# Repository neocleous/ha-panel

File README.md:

# Home Assistant Touch Panel

A desk-mounted Home Assistant touch panel, vibe coded from start to finish — the software in this repo was written end-to-end by an AI assistant (Claude) in conversation with the maintainer, hardware debugging included. Read it with that in mind; it runs a real panel every day, but nobody hand-crafted it.

Built on a Raspberry Pi 5 with a Waveshare 8" DSI touchscreen, environmental sensors, capacitive touch buttons, and a 3D-printable desk-stand enclosure ([STEP file](https://github.com/neocleous/ha-panel/blob/docs/enclosure/HA%20Panel%20Final.step) on the `docs` branch). Home Assistant runs on a separate server — each panel is a pure display and sensor client, no HAOS on the panel itself.

## What it does

- **Kiosk dashboard** — Chromium in app mode under labwc (Wayland), portrait, no window chrome, with a working on-screen keyboard (squeekboard)
- **Screen sleep** — backlight off after touch inactivity; the wake tap is swallowed via an evdev grab so it never presses anything in the UI
- **Auto-brightness** — backlight follows ambient light from the VEML6030, delivered over MQTT
- **Dark mode** — follows sunset/sunrise via a retained MQTT topic published by an HA automation; Chromium restarts with `--force-dark-mode`
- **Environmental sensors** — temperature, humidity, pressure, VOC (BME680) and ambient light, auto-registered in HA via MQTT discovery
- **Physical buttons** — four capacitive touch buttons (AT42QT1070 on a custom PCB) that work even with the screen asleep
- **Self-updating** — nightly systemd timer runs a full unattended OS + firmware + repo update, showing a progress splash if anyone touches the screen mid-update
- **Zero-touch provisioning** — the [Panel Setup](tools/panel-setup/) app writes first-boot files to a freshly flashed SD card; the panel installs itself and boots into the dashboard in 10–15 minutes (two reboots)

## Hardware

Full parts list with sourcing links: **[BOM.md](BOM.md)**

| Component | Part |
|-----------|------|
| Compute | Raspberry Pi 5 (4 GB) |
| Display | Waveshare 8inch DSI LCD (C), 1280×800 IPS, portrait |
| Touch buttons | AT42QT1070 on a custom PCB (I2C 0x1B, 4 capacitive electrodes) |
| Temp / humidity / pressure / VOC | BME680 breakout (I2C 0x77) |
| Ambient light | VEML6030 breakout (I2C 0x48) |
| Proximity | VL53L0X breakout (I2C 0x29) |
| Power | USB-C (Adafruit USB Type C vertical breakout) |
| Enclosure | 3D-printed desk stand — STEP on the `docs` branch |

All sensors sit on the Pi's I2C bus 1. The sensor cluster lives at the base of the stand, ventilated top-to-bottom, away from display/Pi heat.

## Deploying a panel

The easy way — **[Panel Setup](tools/panel-setup/)** (macOS / Windows / Linux, single binary, no dependencies):

1. Flash Raspberry Pi OS Lite (64-bit) with Raspberry Pi Imager — **no** Imager customisation
2. Run Panel Setup, fill the form (it tests your MQTT credentials against the broker and your Home Assistant URL before letting you write)
3. It writes `userconf.txt`, `firstrun.sh` and the first-boot hook in `cmdline.txt` to the SD card
4. Insert, power on, wait 10–15 minutes. The first boot configures the panel and reboots; the second installs everything (progress on screen) and reboots into your dashboard. Logs: `firstrun.log` and `firstboot.log` on the SD card — details in [tools/panel-setup/README.md](tools/panel-setup/README.md#what-the-first-boot-does)

Binaries on the [Releases page](../../releases); build details and the unsigned-app first-run notes are in [tools/panel-setup/README.md](tools/panel-setup/README.md).

The manual way — SSH install with `system/install.sh` — is documented in [system/README.md](system/README.md).

## Repository layout

```
ha-panel/
├── sensor-daemon/        # MQTT discovery + I2C polling (systemd service)
│   └── sensors/          # AT42QT1070, BME680, VL53L0X, VEML6030 drivers
├── system/               # Kiosk stack: startup.sh, screen-sleep.py,
│                         # nightly update.sh + timer, update splash
├── provisioning-ui/      # On-device touchscreen setup wizard
└── tools/panel-setup/    # Cross-platform SD-card preparation app (Go)
```

Per-panel state lives outside the repo on the device (`/opt/ha-panel/config` and `/opt/ha-panel/sensor-config.py`) and survives the nightly `git reset --hard`. **Never commit credentials to this repo.**

## How the kiosk works

```
TTY1 autologin (.bash_profile)
  └── startup.sh
        ├── sources /opt/ha-panel/config
        ├── writes labwc rc.xml   (touch→output mapping, undecorated maximised windows)
        ├── writes labwc autostart (screen-sleep, squeekboard, chromium loop)
        └── exec labwc
              ├── screen-sleep.py  (sleep/wake + auto-brightness + theme switch)
              ├── squeekboard      (on-screen keyboard)
              └── chromium --app=<HA dashboard>  (restarts on crash/theme/update)
```

MQTT topics follow `home/<panel-id>/…`; the fleet-wide dark-mode topic is `home/panels/theme`.

## SSH access

Panels accept SSH from the local /24 only (nftables). `ssh you@panel-01.local`.

## Troubleshooting

First stops: `/var/log/ha-panel-startup.log` on the panel, `journalctl -u sensor-daemon`, `/var/log/ha-panel-update.log` for the nightly update, and `firstrun.log` / `firstboot.log` on the SD card's boot partition if first boot fails. More in [system/README.md](system/README.md).

## License

[PolyForm Noncommercial 1.0.0](LICENSE.md) — free for personal, hobby, educational, and other noncommercial use: build panels, modify the code, share it. **Commercial use is not permitted.** If you want to use this commercially, contact the maintainer about a separate license.

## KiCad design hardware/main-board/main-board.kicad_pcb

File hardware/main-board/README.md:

# HA panel — main board

> **Rev 3.2 (2026-11-14): the board in this folder.** Rev 3.1 with a relief in the side edge on the left-speaker side
> (floor at u +42.0 over v +1.5 ... +13.0, 1.5 deep, inner corners r 1.0) for the ReSpeaker's USB-C plug and the pliers
> that pull it. No part moved; the amplifier's GPIO2 via and the I2C pair's loop on the back face were laid inside the
> new edge, and the pours follow it (Daniel's decision of 2026-11-14). ERC 0 errors 0 warnings; DRC 0 errors, 0 open
> connections, schematic comparison clean, 2 warnings. Report: [`rev3.2/README.md`](rev3.2/README.md). For the enclosure
> model: [`main-board-rev3-2-reply-2026-11-14.md`](main-board-rev3-2-reply-2026-11-14.md), [`MAIN_env.md`](MAIN_env.md),
> `main-board-rev3.2.step`; the plug envelopes of rev 3.1 stand (`main-board-rev3.1-plug-envelopes.step`). Rev 3.1's
> files are kept (`rev3.1/`, `main-board-rev3.1.step`, `main-board-rev3.1-plug-envelopes.step`,
> `main-board-rev3-1-reply-2026-11-11.md`). No fab files for rev 3, 3.1 or 3.2.
>
> **Rev 3.1 (2026-11-11): its board file is now `rev3.1/main-board-rev3.1.kicad_pcb`.** Rev 3 with three changes asked for by the enclosure (top right
> hole at u +19.20, v +25.00; BME680 header 3.90 further from the radar socket; VEML6030 header 1.00 lower), wider
> copper for the Pi's 5 V and the 20 V inlet, and ground pours on both outer layers. Same circuit, same parts.
> ERC 0 errors 0 warnings; DRC 0 errors, 0 open connections, schematic comparison clean, 2 warnings.
> Report: [`rev3.1/README.md`](rev3.1/README.md). For the enclosure model:
> [`main-board-rev3-1-reply-2026-11-11.md`](main-board-rev3-1-reply-2026-11-11.md), [`rev3.1/MAIN_env.md`](rev3.1/MAIN_env.md),
> `main-board-rev3.1.step`, `main-board-rev3.1-plug-envelopes.step`. Pi lead table: [`gpio-leads.md`](gpio-leads.md).
> The rev 3 files are kept (`rev3/`, `main-board-rev3.step`, `main-board-rev3-plug-envelopes.step`,
> `main-board-rev3-reply-2026-11-11.md`). No fab files for rev 3 or rev 3.1.
>
> **Rev 3 (2026-11-11): schematic and routed board for the site behind the display.**
> 87.0 x 57.9, four layers, every part on the door side. ERC 0 errors 0 warnings; DRC 0 errors, 0 open connections,
> schematic comparison clean, 2 warnings. Report: [`rev3/README.md`](rev3/README.md) (floor plan: sections 1 to 13, routed
> board: section 14). Pi lead table: [`rev3/gpio-leads.md`](rev3/gpio-leads.md). For the enclosure model:
> [`main-board-rev3-reply-2026-11-11.md`](main-board-rev3-reply-2026-11-11.md), [`rev3/MAIN_env.md`](rev3/MAIN_env.md),
> `main-board-rev3.step`, `main-board-rev3-plug-envelopes.step`. The board file of rev 3 is
> `rev3/main-board-rev3.kicad_pcb`.
> **Everything below this note describes rev 2.1**, whose files are now in [`rev2.1/`](rev2.1/). All of it is a draft
> until the whole unit is shown to be buildable (architect log 2026-11-10, section 0).

Status: **block 3 done (2026-11-09) — layout rev 2.1, single-sided SMD, routed, DRC clean; fab files, BOM, assembly notes and drawing issued.** Rev 2.1 moves C7 to the top strip so every front lead plugs after mounting (`MAIN_env.md`).

- **KiCad 9.0.9.** Open `main-board.kicad_pro`. Project libraries: `lib/ha_panel.kicad_sym` (custom symbols: TAS5756M, TPS16630, NID100-5, TPS70933, +20V power symbol) and `lib/ha_panel.pretty` (custom footprints, created in block 2).
- **Schematic PDF:** `main-board-schematic.pdf` (5 pages).
- **ERC:** 0 errors, 0 warnings (`erc-report.txt`). **DRC:** 0 errors, 0 unconnected, parity clean, 2 warnings (J2 silk trimmed at the board edge, J4 courtyard trimmed to its wire pads) (`drc-report.txt`).
- **Board:** 90 × 55, 4 layers (F parts + signals / In1 GND / In2 +5V, +20V, PVDD / B signals). Every SMD part on the front; the back carries only J2, LK1, through-hole joints and bare test pads. Renders: `main-board-routed-3d.png` (front, back), `main-board-copper-F-B.png` (front copper, back copper mirrored). Layout notes: `NOTES.md` §7; envelope: `MAIN_env.md`.
- **Fab (JLC, bare board):** `fab/main-board-jlc-2026-11-08.zip`; order options and what the files use against JLC's limits in `../notes/jlc-fab.md`. **Stencil:** the main-board area of the combined stencil `../stencil/` (D57).
- **Assembly drawing:** `main-board-assembly.pdf` (A3; front and back, DNP crossed out), from `gen/assembly_drawings.py`. Assembly and bring-up: below.
- **Notes with every value's source:** `NOTES.md`. **GPIO lead pin table and plug maps:** `gpio-leads.md`.
- `gen/` holds the Python that generated the schematic and the layout (sheet builder, footprints, placement, TAS escape, maze router, Freerouting driver, silk placement). The KiCad files are the source of truth; the scripts are kept for provenance (symbol UUIDs are deterministic, so a schematic regeneration keeps the PCB links; a layout regeneration routes differently, see NOTES §7).

## Sheets
1. Root — index.
2. **20 V inlet and eFuse** — J1 (5807 pigtail) → F1 0453005.MR → TPS16630 (UVLO 17.05 V, OVP 24.06 V, I_OL 3.28 A, dV/dt 19.6 ms) → +20V bus with SMBJ22A.
3. **5 V supply and outputs** — Mean Well EMC circuit (120 µF – SRR1260-150M – 120 µF) → NID100-5 (enabled by the eFuse PGOOD) → 22 µF + SMBJ6.0A-E → Pi branch (0453010.MR → wire link LK1 → USB4085-GF-A, Rp 10 kΩ) and radar branch (0453001.MR). DNP trim network R8/R9.
4. **3.3 V, Pi link, XH, D4a** — TPS70933 LDO (EN = Pi 3V3) → sensor PTC and amp logic rail; GPIO landing J3/J4 (13 wire pads); radar and touch XH headers; D4a ReSpeaker tap J7 with six DNP 0 Ω links.
5. **Amplifier** — TAS5756M stereo BTL per SLAS988B Fig. 79 / Table 22 with the DigiAMP+ wiring (`rpi-digiampplus`: I²C 0x4C, GPIO22 mute), 20 dBV at 768 kHz, type-2 LC 10 µH + 0.68 µF, speaker XH headers.

## Default fit (spin 1)
| Option | Default | Alternative |
|---|---|---|
| Echo reference (D4a) | **Topology A, USB reference**: R20–R25 open | Topology B, I²S reference: fit R20–R23 (+R24/R25), I²S firmware, Pi as I²S clock consumer |
| NID trim (V20) | R8, R9 open (5.0 V) | R8 Trim→Com raises Vout; value found on the bench via TP13 |
| Amp logic rail | R26 fitted (board LDO) | R27 instead of R26 (Pi 3V3) |
| I²S series | R14–R16 0 Ω | 22–47 Ω if edges ring |
| NID enable | R7 0 Ω (eFuse PGOOD) | R7 open = NID free-running |
| Pi branch | LK1 wire fitted | LK1 open + 10 A meter (bench 2.7) |

## Assembly (block 3, 2026-11-09)
One hotplate pass for every SMD part (front), then the THT parts with the iron. Drawing: `main-board-assembly.pdf`.

**Before you start**
- Paste: Sn63/Pb37 no-clean, as on rev C (Chip Quik SMD291AXT4, `hardware/rev-c/README.md`). Stencil: the main-board area of `../stencil/`, 0.12 mm.
- U100 (TAS5756M) is MSL 3: "Level-3-260C-168 HR" (TI package option addendum in the datasheet), i.e. 168 h at ≤ 30 °C / 60 % RH once its moisture bag is open. Open the bag on build day. If it has been open longer, bake per J-STD-033 before reflow.
- Bare board, meter on ohms: +20V (TP2), PVDD (F5 pin 2), +5V (TP9) and 3V3 (TP16) to GND (TP7) must read open.

**Build order**
1. Paste the front through the stencil. Place every SMD part except the DNPs: R8, R9, R20–R25, R27 (crossed out on the drawing).
   - Polarity: D1 SMBJ22A, D2 SMBJ6.0A-E (band = cathode).
   - Pin 1: U1 TPS16630, U2 TPS70933, U100 TAS5756M (chamfered corner on the drawing).
2. Hotplate with the back down (nothing is on the back yet). Profile below.
3. Inspect U100 (0.5 mm pitch) and U1 (0.65 mm) under magnification for bridges and lifted pins.
4. Iron, door side first, because these joints are on the front among the SMD parts:
   - J2 USB4085 (16 contacts, 4 shell stakes), mouth flush with the bottom edge;
   - LK1, 1.0 mm tinned copper wire.
5. Iron, front parts soldered on the back, low to high: J10 (2 × 4 header), J1, J5, J6, J8, J9 (XH), C7, C5, C6 (+ to the + mark), PS1 NID100-5 last.
6. J3/J4 take the GPIO lead wires (`gpio-leads.md`, `../notes/harness.md`). J7 stays empty in topology A.

**Hotplate profile**
- Follow the paste maker's profile. Chip Quik's chart for SMD291AX (datasheet rev 1.1) runs 25 → 100 → 150 °C (preheat and soak), crosses the 183 °C liquidus and tops at 235 °C, about 240 s in all.
- U100 is rated 260 °C peak (TI, above), so a Sn63/Pb37 profile stays below its limit.
- Thermal pad (pin 49): the stencil's 2 × 4 windows give 72.8 % paste coverage. SLAS988B 11.1.3.2 asks for 70–80 %. The 39 vias under the pad are in the footprint.
- The paste's flux is "Synthetic No-Clean" (Chip Quik), so nothing is washed.

**Default fit:** the table above. All D4a links open (topology A), R26 fitted, LK1 fitted.

## Bring-up (bench, board out of the enclosure)
Meter only; test pads are on the back (`NOTES.md` §5). Ground: TP7, TP15, TP17 or TP20.

**Stage 1: 20 V only.** The 5807 + charger on J1; no Pi, leads or sensors.

| Probe | Expect | Why |
|---|---|---|
| TP1 VIN, TP2 20V, TP8 NID_IN, F5 pin 2 (PVDD; front, bench only) | ≈ 20 V, all equal | eFuse on above UVLO 17.05 V; OVP at 24.06 V (`NOTES.md` §1) |
| TP3 IMON | 0.279 V/A × bus current: record it | eq. 9, `NOTES.md` §1 |
| TP6 SHDN | ≈ 2.7 V | internal open-circuit voltage (SLVSET9G 6.5) |
| TP9 5V; TP10 5V_F, TP11 EXT5V, TP12 RADAR | 4.90–5.10 V, all ≈ equal | NID100-5 ± 2 % (bench plan 2.12) |
| TP13 TRIM | record (V20) | `NOTES.md` §2 |
| TP16 3V3, TP19 FAULT, TP4 FLT | ≈ 0 V | The LDO waits for the Pi's 3V3 on lead A1 (EN, R13 pull-down); FLT and FAULT are pulled up to rails that are still off. |

**Stage 2: Pi on.**
- Connect:
  - J2 → Pi USB-C;
  - GPIO plugs A and B;
  - the LCD lead per `../notes/harness.md`: 5 V and GND at Pi pins 2/6. Insulate and tie back its SDA/SCL wires (V22).
- Expect:

| Probe | Expect | Why |
|---|---|---|
| TP16 3V3 | 3.267–3.333 V | TPS70933 ± 1 % (SBVS186H) |
| TP4 FLT, TP19 FAULT | ≈ 3.3 V | no eFuse fault, no amp fault |
| `vcgencmd get_throttled` | `0x0` | bench plan 2.6 |
| `vcgencmd pmic_read_adc EXT5V_V` | ≥ 4.87 V under load | bench plan 2.6 |

**Stage 3: config and buses.** Apply `../notes/pi-config.md`, then plug the sensors (J10), the touch lead (J6) and the radar (J5).
- `sudo i2cdetect -y 1`: **1b** (touch), **48** (VEML6030), **UU** at 4c (TAS5756M, held by the `rpi-digiampplus` driver), **77** (BME680).
- Radar: record TP12 with the LD2410C running (the rail's worst case is 4.90 V; the LD2410C manual gives 5–12 V). Expect 0 invalid frames at 256000 8N1 on `/dev/ttyAMA0` (bench plan 1.5, 2.12).
- Then bench plan stage 2 (2.1–2.12).

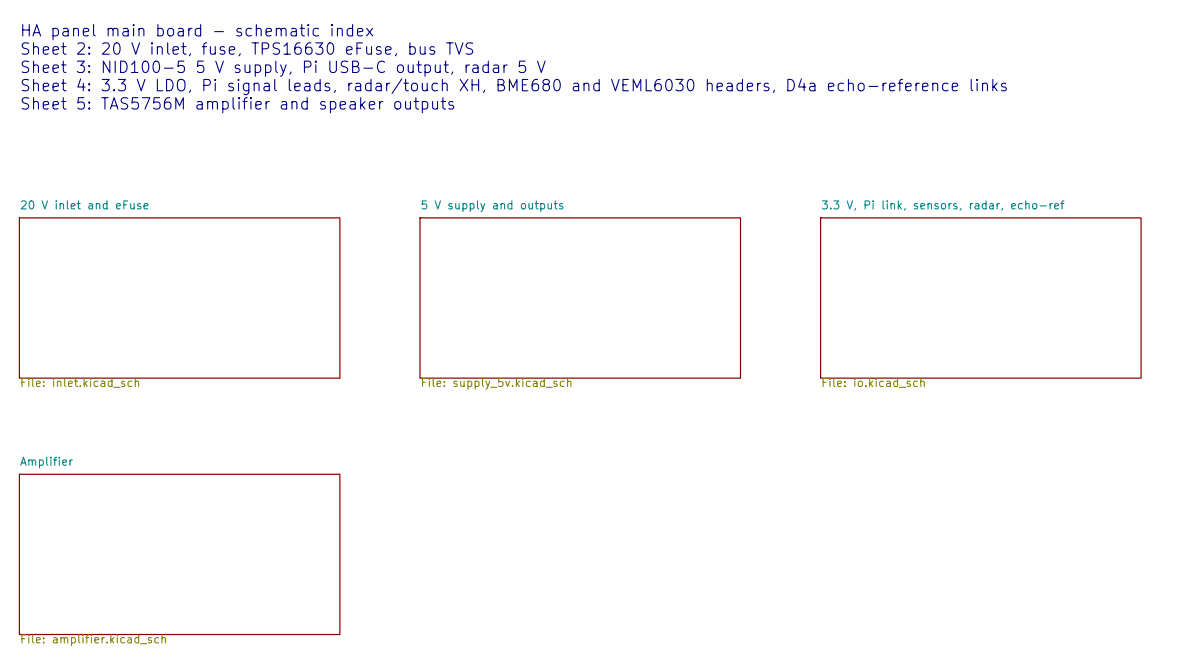
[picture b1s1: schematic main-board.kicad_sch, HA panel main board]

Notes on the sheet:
HA panel main board - schematic index Sheet 2: 20 V inlet, fuse, TPS16630 eFuse, bus TVS Sheet 3: NID100-5 5 V supply, Pi USB-C output, radar 5 V Sheet 4: 3.3 V LDO, Pi signal leads, radar/touch XH, BME680 and VEML6030 headers, D4a echo-reference links Sheet 5: TAS5756M amplifier and speaker outputs

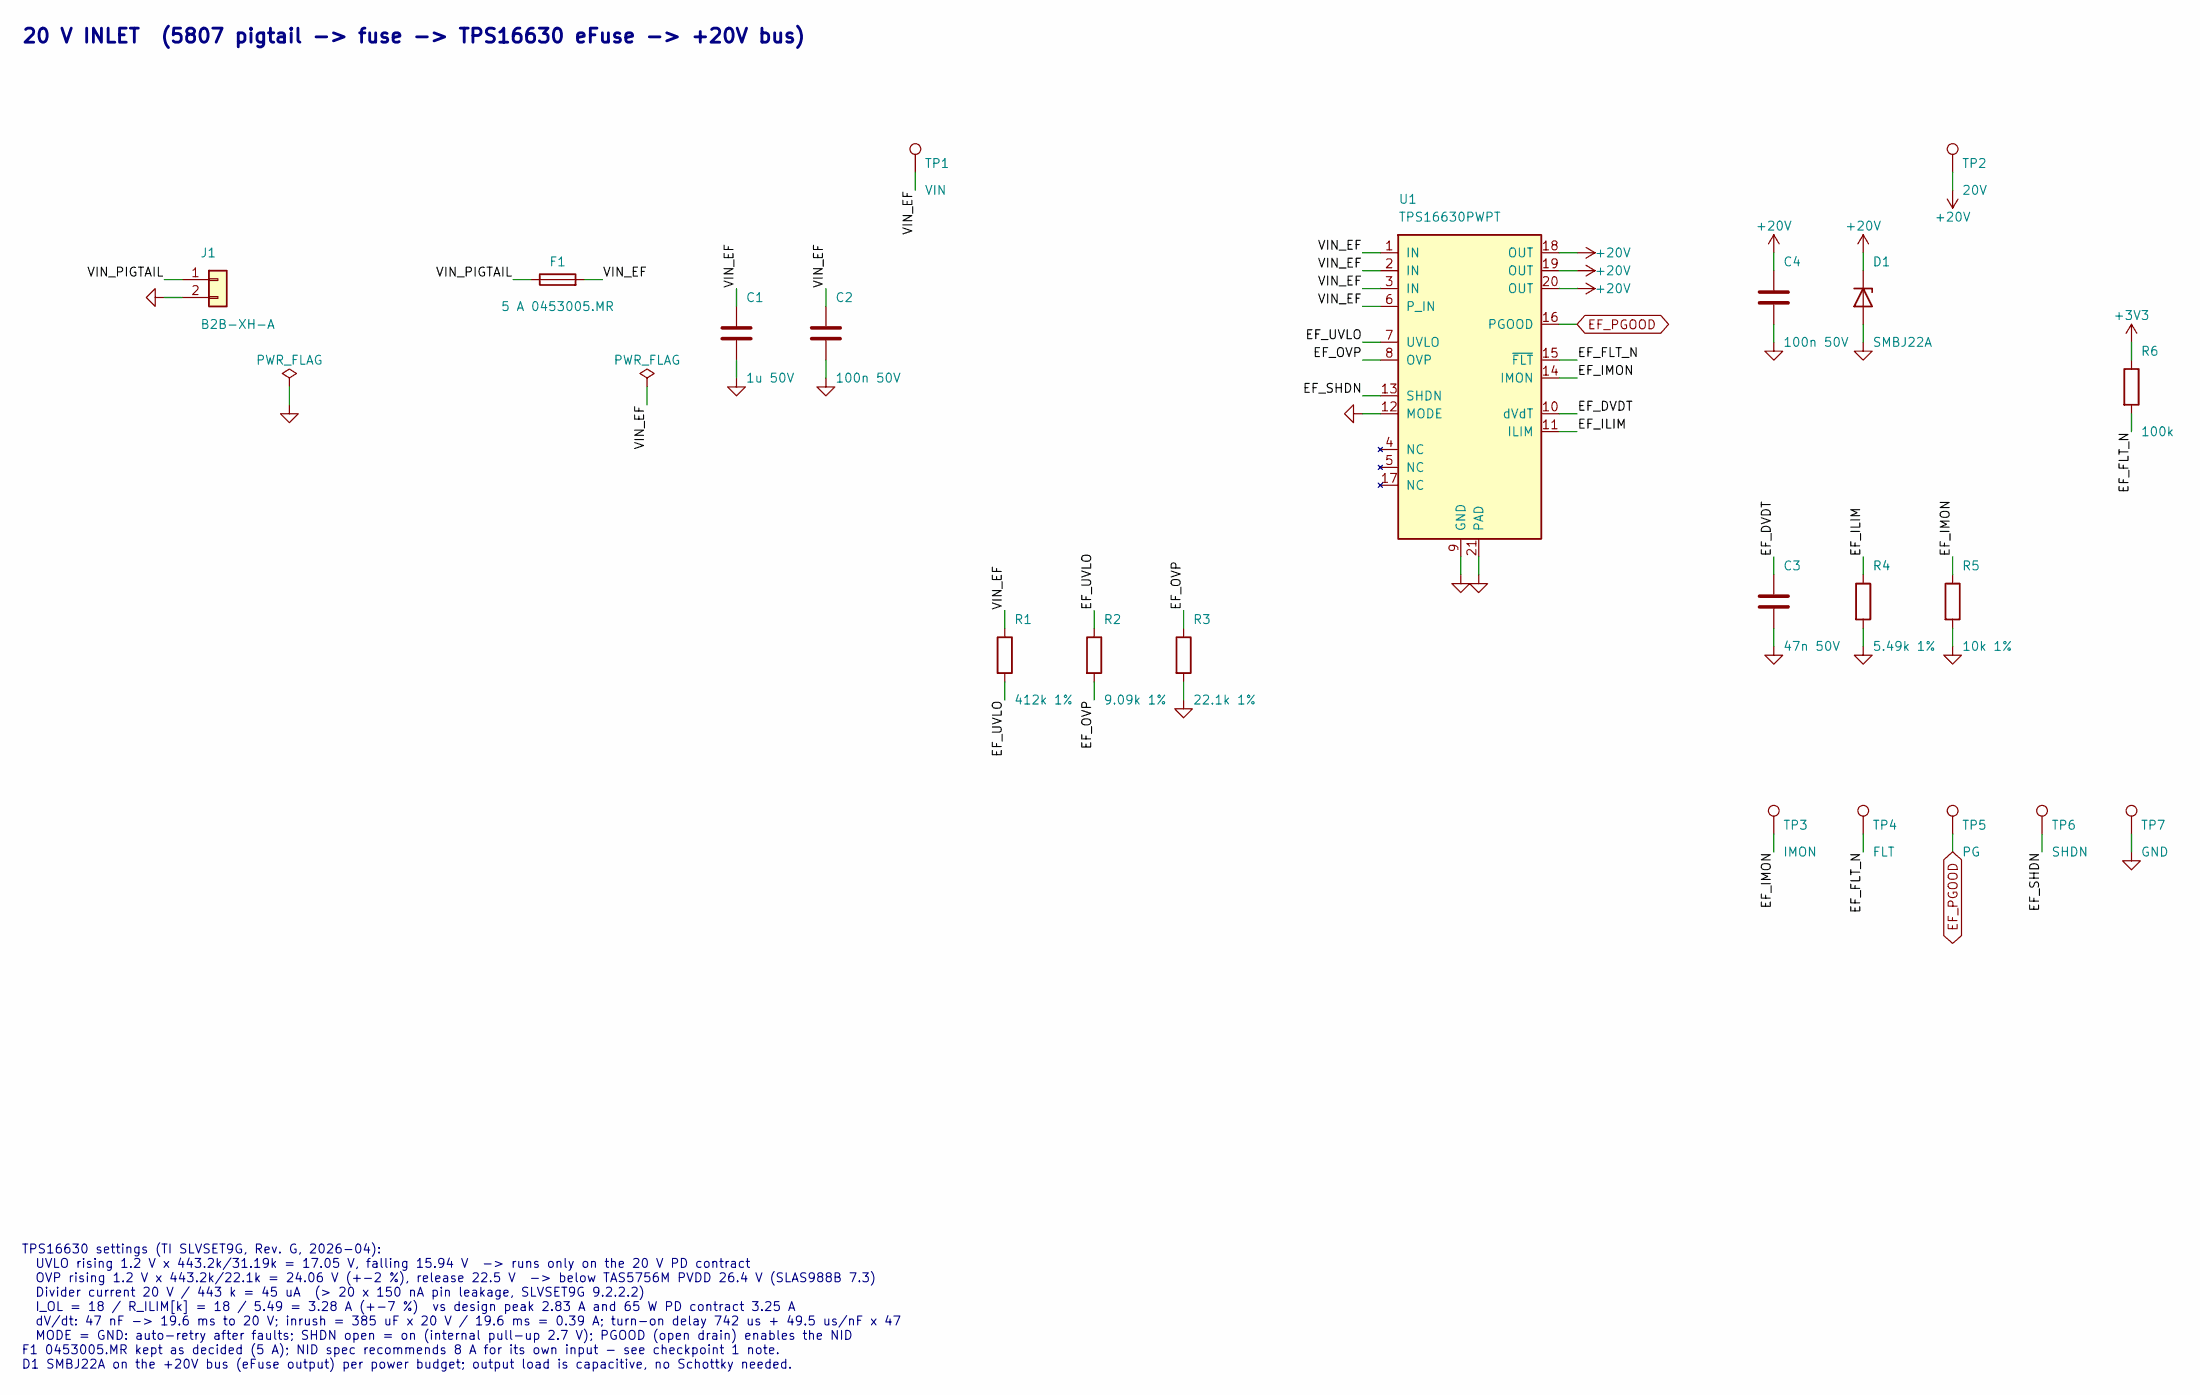
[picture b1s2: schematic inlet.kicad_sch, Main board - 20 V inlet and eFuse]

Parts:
C1: 1u 50V; C_0805_2012Metric; MPN 08055C105KAT2A; DigiKey 478-KGM21AR71H105KUCT-ND
C2, C4: 100n 50V; C_0603_1608Metric; MPN CC0603KRX7R9BB104; DigiKey 311-1344-1-ND
C3: 47n 50V; C_0603_1608Metric; MPN CL10B473KB8NNNC; DigiKey 1276-1063-1-ND
D1: SMBJ22A; D_SMB; MPN SMBJ22A; DigiKey SMBJ22ALFCT-ND
F1: 5 A 0453005.MR; Fuse_Littelfuse-NANO2-451_453; MPN 0453005.MR; DigiKey F3139CT-ND
J1: B2B-XH-A; JST_XH_B2B-XH-A_1x02_P2.50mm_Vertical; MPN B2B-XH-A; DigiKey 455-B2B-XH-A-ND
R1: 412k 1%; R_0603_1608Metric; MPN RC0603FR-07412KL; DigiKey 311-412KHRCT-ND
R2: 9.09k 1%; R_0603_1608Metric; MPN RC0603FR-079K09L; DigiKey 311-9.09KHRCT-ND
R3: 22.1k 1%; R_0603_1608Metric; MPN RC0603FR-0722K1L; DigiKey 311-22.1KHRCT-ND
R4: 5.49k 1%; R_0603_1608Metric; MPN RC0603FR-075K49L; DigiKey 311-5.49KHRCT-ND
R5: 10k 1%; R_0603_1608Metric; MPN RMCF0603FT10K0; DigiKey RMCF0603FT10K0CT-ND
R6: 100k; R_0603_1608Metric; MPN RMCF0603FT100K; DigiKey RMCF0603FT100KCT-ND
TP1: VIN; TestPoint_Pad_D1.5mm
TP2: 20V; TestPoint_Pad_D1.5mm
TP3: IMON; TestPoint_Pad_D1.5mm
TP4: FLT; TestPoint_Pad_D1.5mm
TP5: PG; TestPoint_Pad_D1.5mm
TP6: SHDN; TestPoint_Pad_D1.5mm
TP7: GND; TestPoint_Pad_D1.5mm
U1: TPS16630PWPT; HTSSOP-20-1EP_4.4x6.5mm_P0.65mm_EP3.4x6.5mm_Mask2.96x2.96mm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; MPN TPS16630PWPT; DigiKey 296-TPS16630PWPTCT-ND

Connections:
+3V3: R6.1; also elsewhere on the board
+20V: C4.1, D1.1 (K), TP2.1, U1.18 (OUT), U1.19 (OUT), U1.20 (OUT); also elsewhere on the board
/20 V inlet and eFuse/EF_DVDT: C3.1, U1.10 (dVdT)
/20 V inlet and eFuse/EF_FLT_N: R6.2, TP4.1, U1.15 (~FLT)
/20 V inlet and eFuse/EF_ILIM: R4.1, U1.11 (ILIM)
/20 V inlet and eFuse/EF_IMON: R5.1, TP3.1, U1.14 (IMON)
/20 V inlet and eFuse/EF_OVP: R2.2, R3.1, U1.8 (OVP)
/20 V inlet and eFuse/EF_SHDN: TP6.1, U1.13 (SHDN)
/20 V inlet and eFuse/EF_UVLO: R1.2, R2.1, U1.7 (UVLO)
/20 V inlet and eFuse/VIN_EF: C1.1, C2.1, F1.2, R1.1, TP1.1, U1.1 (IN), U1.2 (IN), U1.3 (IN), U1.6 (P_IN)
/20 V inlet and eFuse/VIN_PIGTAIL: F1.1, J1.1
EF_PGOOD: TP5.1, U1.16 (PGOOD); also elsewhere on the board
GND: C1.2, C2.2, C3.2, C4.2, D1.2 (A), J1.2, R3.2, R4.2, R5.2, TP7.1, U1.9 (GND), U1.12 (MODE), U1.21 (PAD); also elsewhere on the board

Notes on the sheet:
20 V INLET (5807 pigtail -> fuse -> TPS16630 eFuse -> +20V bus)
TPS16630 settings (TI SLVSET9G, Rev. G, 2026-04): UVLO rising 1.2 V x 443.2k/31.19k = 17.05 V, falling 15.94 V -> runs only on the 20 V PD contract OVP rising 1.2 V x 443.2k/22.1k = 24.06 V (+-2 %), release 22.5 V -> below TAS5756M PVDD 26.4 V (SLAS988B 7.3) Divider current 20 V / 443 k = 45 uA (> 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

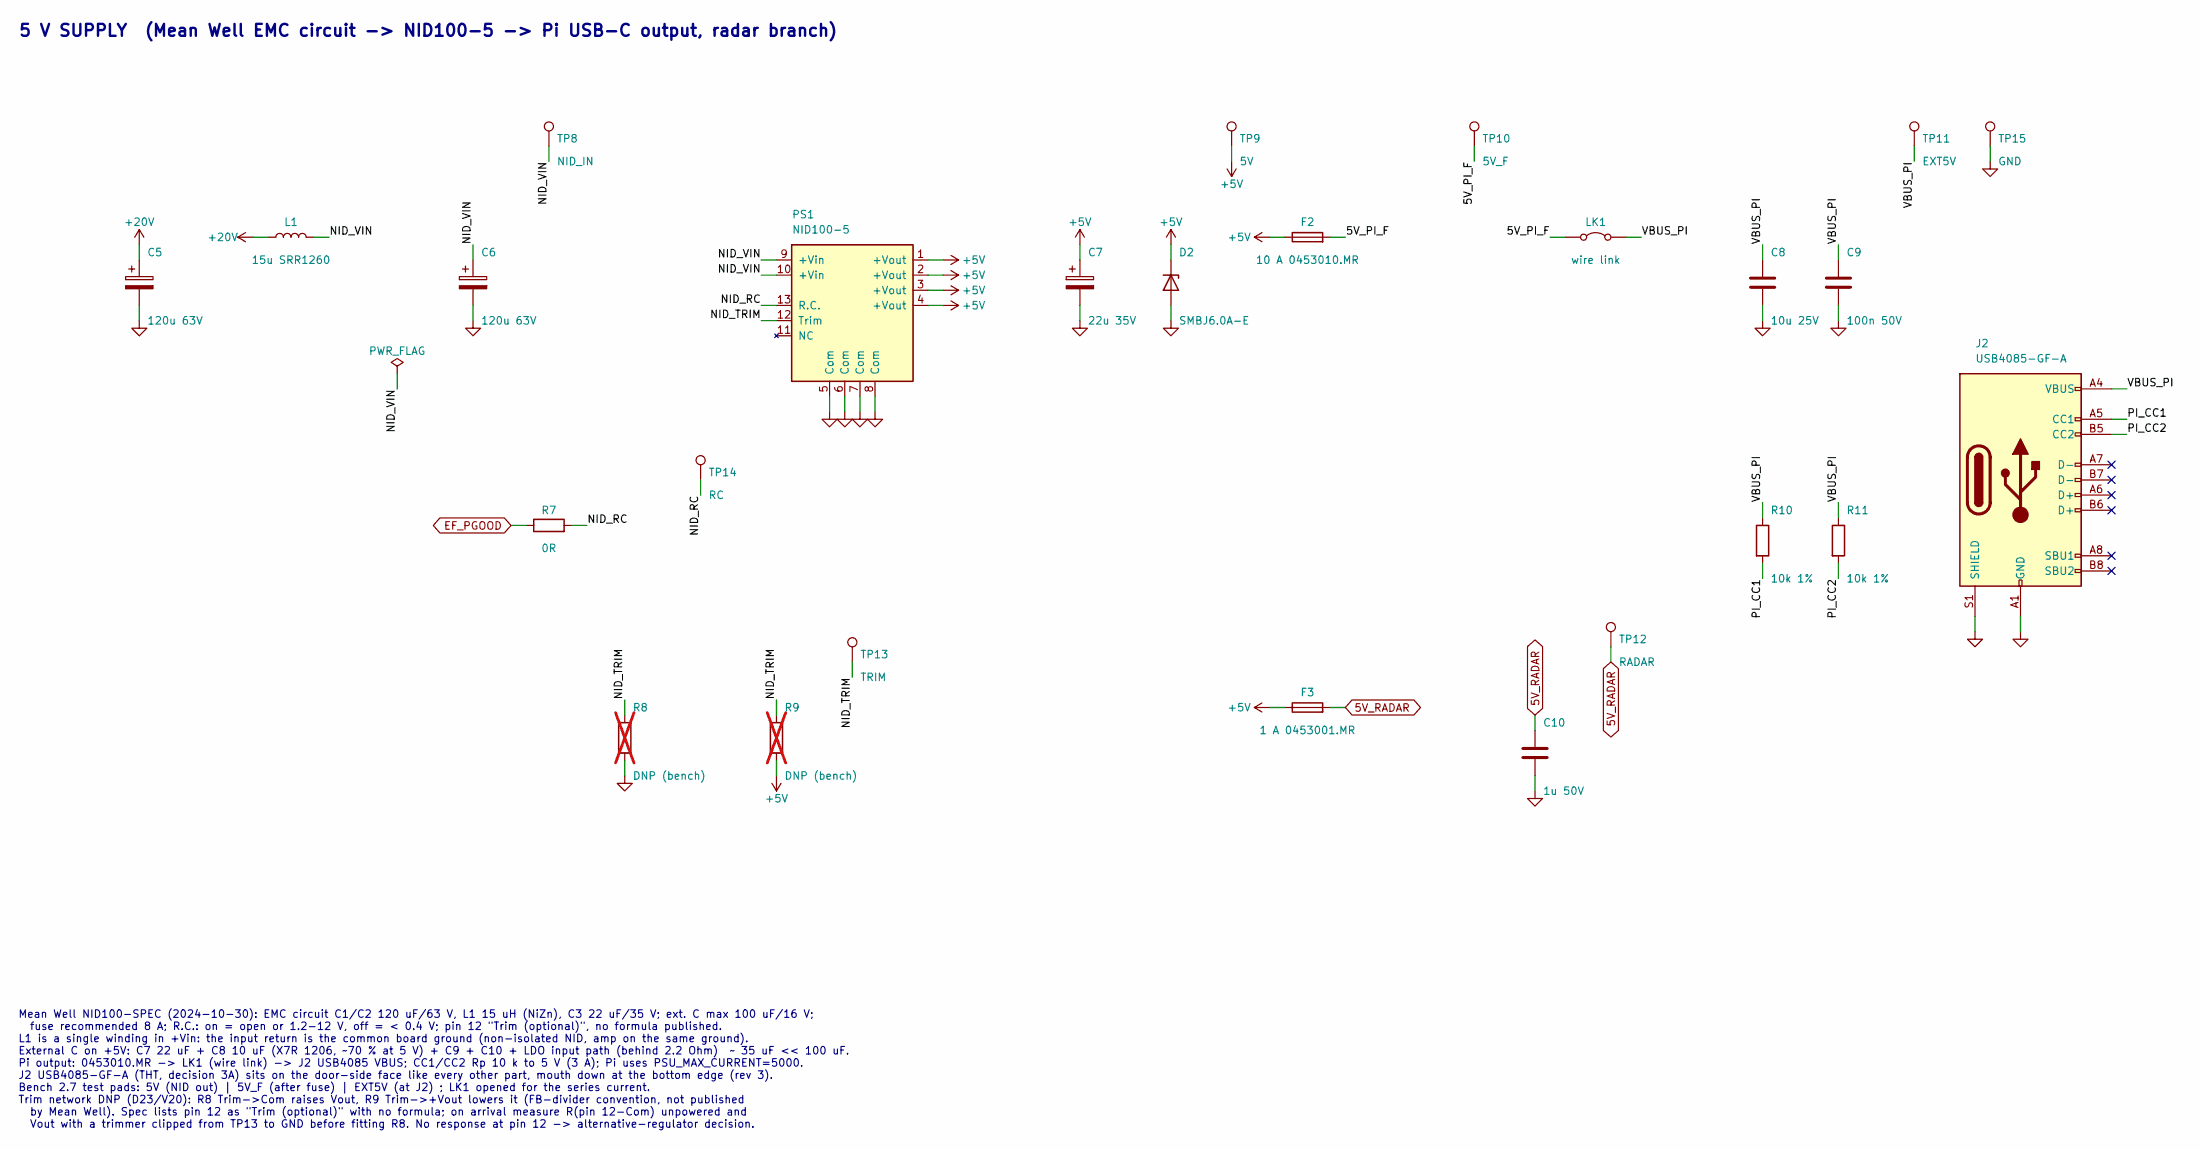
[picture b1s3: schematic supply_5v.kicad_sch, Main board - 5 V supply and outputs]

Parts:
C5, C6: 120u 63V; CP_Radial_D10.0mm_P5.00mm; MPN EEU-FR1J121B; DigiKey P15289CT-ND
C7: 22u 35V; CP_Radial_D5.0mm_P2.00mm; MPN 860160572003; DigiKey 732-9541-1-ND
C8: 10u 25V; C_1206_3216Metric; MPN C1206C106K4RACTU; DigiKey 399-C1206C106K4RACTUCT-ND
C9: 100n 50V; C_0603_1608Metric; MPN CC0603KRX7R9BB104; DigiKey 311-1344-1-ND
C10: 1u 50V; C_0805_2012Metric; MPN 08055C105KAT2A; DigiKey 478-KGM21AR71H105KUCT-ND
D2: SMBJ6.0A-E; D_SMB; MPN SMBJ6.0A-E; DigiKey 18-SMBJ6.0A-ECT-ND
F2: 10 A 0453010.MR; Fuse_Littelfuse-NANO2-451_453; MPN 0453010.MR; DigiKey F3141CT-ND
F3: 1 A 0453001.MR; Fuse_Littelfuse-NANO2-451_453; MPN 0453001.MR; DigiKey F3137CT-ND
J2: USB4085-GF-A; USB_C_Receptacle_GCT_USB4085; MPN USB4085-GF-A; DigiKey 2073-USB4085-GF-ACT-ND
L1: 15u SRR1260; L_Bourns_SRR1260; MPN SRR1260-150M; DigiKey SRR1260-150MCT-ND
LK1: wire link; WireLink_P7.62mm_D1.3mm
PS1: NID100-5; MeanWell_NID100_SIP-13; MPN NID100-5; DigiKey 1866-NID100-5-ND
R7: 0R; R_0603_1608Metric; MPN RC0603JR-070RL; DigiKey 311-0.0GRCT-ND
R8, R9: DNP (bench); R_0805_2012Metric; not fitted
R10, R11: 10k 1%; R_0603_1608Metric; MPN RMCF0603FT10K0; DigiKey RMCF0603FT10K0CT-ND
TP8: NID_IN; TestPoint_Pad_D1.5mm
TP9: 5V; TestPoint_Pad_D1.5mm
TP10: 5V_F; TestPoint_Pad_D1.5mm
TP11: EXT5V; TestPoint_Pad_D1.5mm
TP12: RADAR; TestPoint_Pad_D1.5mm
TP13: TRIM; TestPoint_Pad_D1.5mm
TP14: RC; TestPoint_Pad_D1.5mm
TP15: GND; TestPoint_Pad_D1.5mm

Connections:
5V_RADAR: C10.1, F3.2, TP12.1; also elsewhere on the board
+5V: C7.1, D2.1 (K), F2.1, F3.1, PS1.1 (+Vout), PS1.2 (+Vout), PS1.3 (+Vout), PS1.4 (+Vout), R9.2, TP9.1; also elsewhere on the board
+20V: C5.1, L1.1; also elsewhere on the board
/5 V supply and outputs/5V_PI_F: F2.2, LK1.1 (A), TP10.1
/5 V supply and outputs/NID_RC: PS1.13 (R.C.), R7.2, TP14.1
/5 V supply and outputs/NID_TRIM: PS1.12 (Trim), R8.1, R9.1, TP13.1
/5 V supply and outputs/NID_VIN: C6.1, L1.2, PS1.9 (+Vin), PS1.10 (+Vin), TP8.1
/5 V supply and outputs/PI_CC1: J2.A5 (CC1), R10.2
/5 V supply and outputs/PI_CC2: J2.B5 (CC2), R11.2
/5 V supply and outputs/VBUS_PI: C8.1, C9.1, J2.A4 (VBUS), J2.A9 (VBUS), J2.B4 (VBUS), J2.B9 (VBUS), LK1.2 (B), R10.1, R11.1, TP11.1
EF_PGOOD: R7.1; also elsewhere on the board
GND: C5.2, C6.2, C7.2, C8.2, C9.2, C10.2, D2.2 (A), J2.A1 (GND), J2.A12 (GND), J2.B1 (GND), J2.B12 (GND), J2.S1 (SHIELD), PS1.5 (Com), PS1.6 (Com), PS1.7 (Com), PS1.8 (Com), R8.2, TP15.1; also elsewhere on the board

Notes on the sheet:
5 V SUPPLY (Mean Well EMC circuit -> NID100-5 -> Pi USB-C output, radar branch)
Mean Well NID100-SPEC (2024-10-30): EMC circuit C1/C2 120 uF/63 V, L1 15 uH (NiZn), C3 22 uF/35 V; ext. C max 100 uF/16 V; fuse recommended 8 A; R.C.: on = open or 1.2-12 V, off = < 0.4 V; pin 12 "Trim (optional)", no formula published. L1 is a single winding in +Vin: the input return is the common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

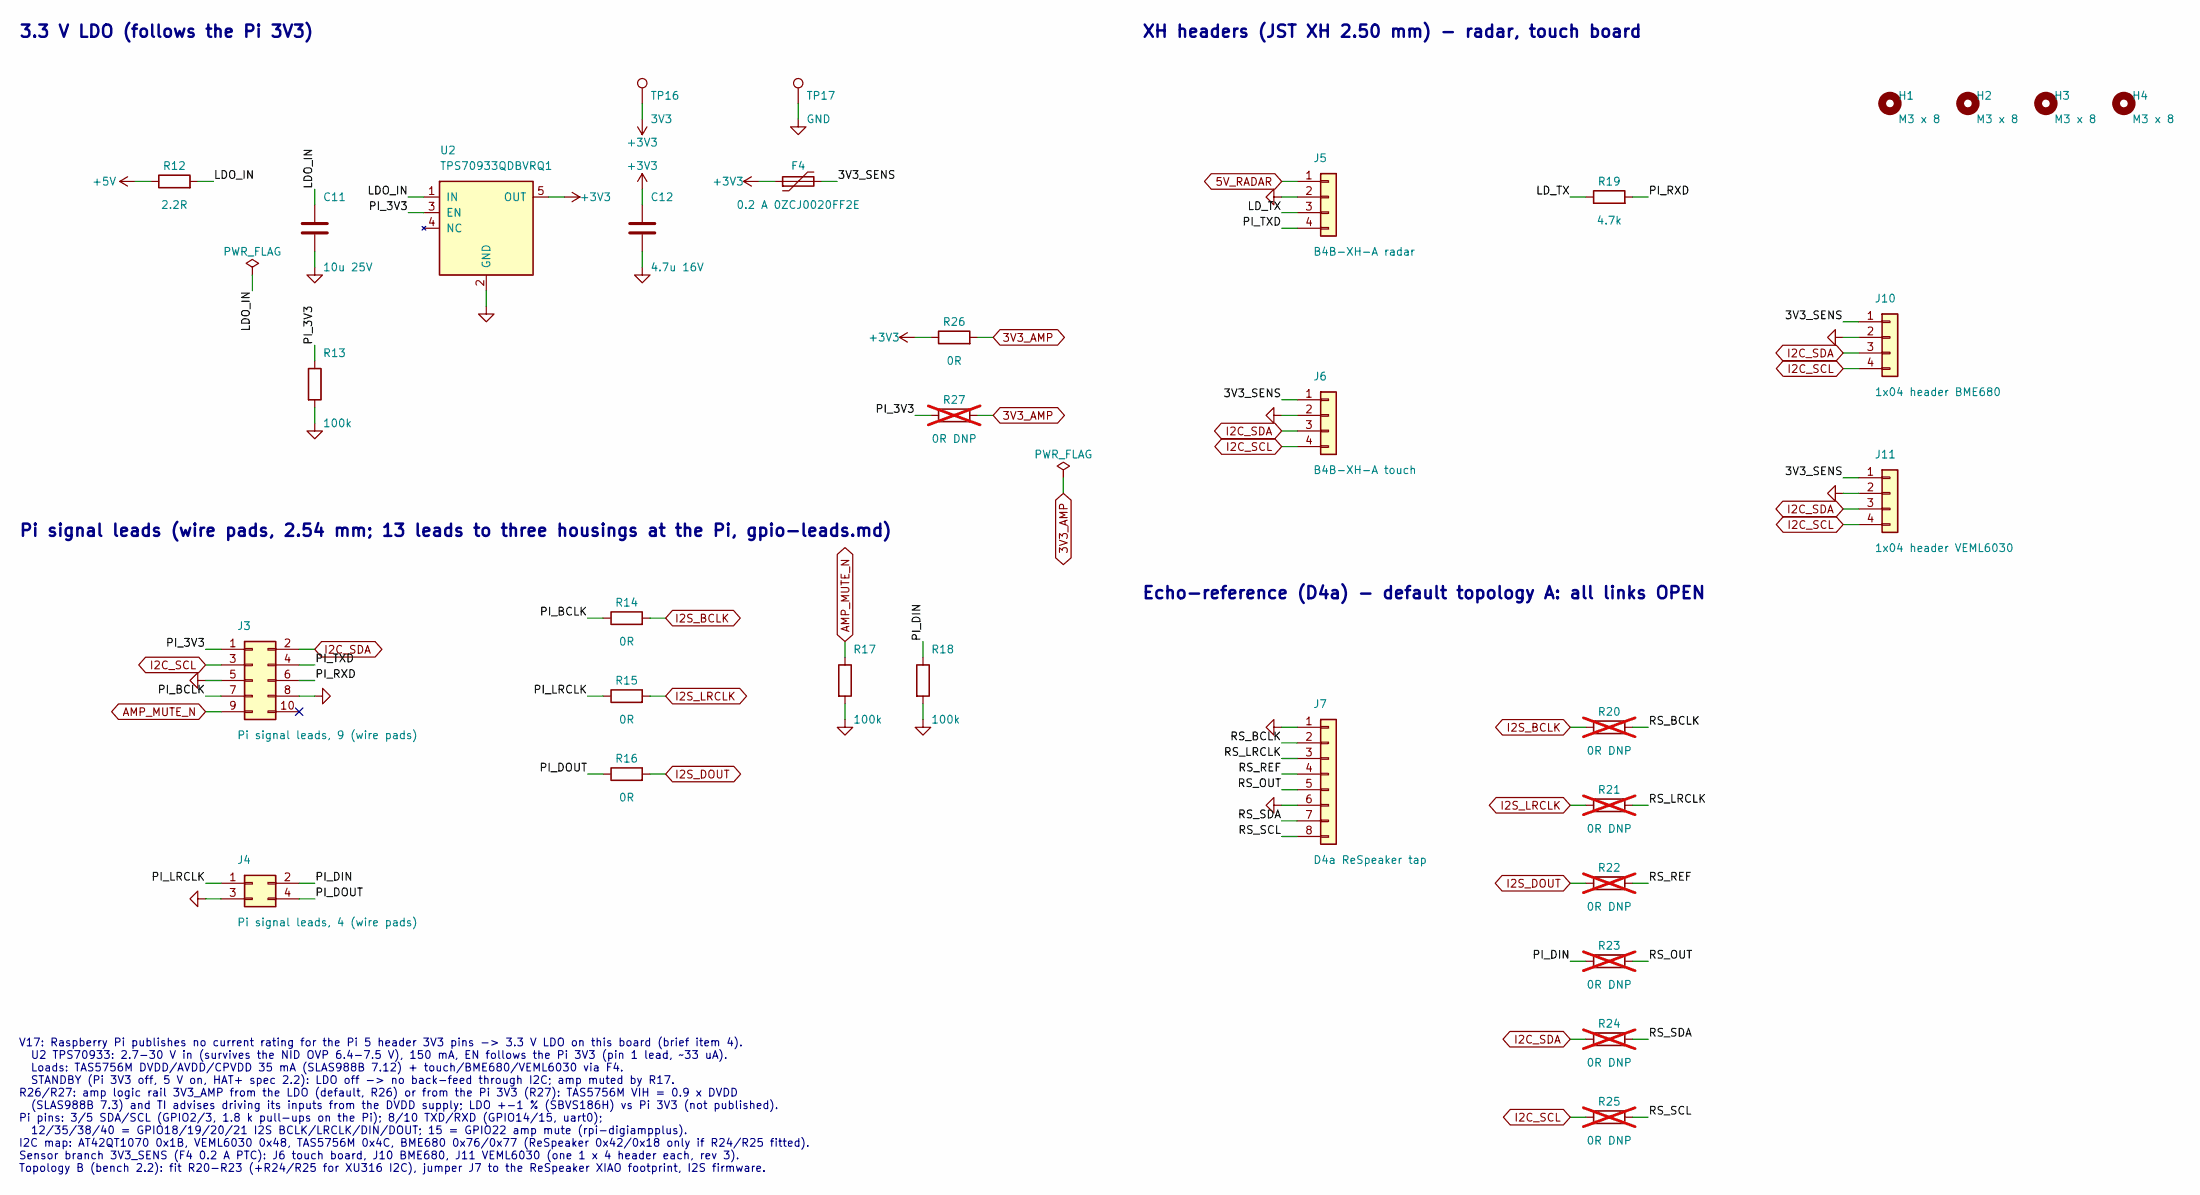
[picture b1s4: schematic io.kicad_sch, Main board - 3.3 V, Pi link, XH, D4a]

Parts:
C11: 10u 25V; C_1206_3216Metric; MPN C1206C106K4RACTU; DigiKey 399-C1206C106K4RACTUCT-ND
C12: 4.7u 16V; C_0805_2012Metric; MPN CL21B475KOFNNNE; DigiKey 1276-2873-1-ND
F4: 0.2 A 0ZCJ0020FF2E; Fuse_1206_3216Metric; MPN 0ZCJ0020FF2E; DigiKey 5923-0ZCJ0020FF2ECT-ND
H1, H2, H3, H4: M3 x 8; MountingHole_3.2mm_M3_Post
J3: Pi signal leads, 9 (wire pads); WirePads_2x05_P2.54mm_D1.0mm
J4: Pi signal leads, 4 (wire pads); WirePads_2x02_P2.54mm_D1.0mm
J5: B4B-XH-A radar; JST_XH_B4B-XH-A_1x04_P2.50mm_Vertical; MPN B4B-XH-A; DigiKey 455-B4B-XH-A-ND
J6: B4B-XH-A touch; JST_XH_B4B-XH-A_1x04_P2.50mm_Vertical; MPN B4B-XH-A; DigiKey 455-B4B-XH-A-ND
J7: D4a ReSpeaker tap; WirePads_1x08_P2.54mm_D1.0mm
J10: 1x04 header BME680; PinHeader_1x04_P2.54mm_Vertical; MPN generic 1 x 4 male pin header, 2.54 mm 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; DigiKey none - not in any basket; chosen with t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
J11: 1x04 header VEML6030; PinHeader_1x04_P2.54mm_Vertical; MPN generic 1 x 4 male pin header, 2.54 mm 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; DigiKey none - not in any basket; chosen with t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
R12: 2.2R; R_0805_2012Metric; MPN RMCF0805FT2R20; DigiKey RMCF0805FT2R20CT-ND
R13, R17, R18: 100k; R_0603_1608Metric; MPN RMCF0603FT100K; DigiKey RMCF0603FT100KCT-ND
R14, R15, R16, R26: 0R; R_0603_1608Metric; MPN RC0603JR-070RL; DigiKey 311-0.0GRCT-ND
R19: 4.7k; R_0603_1608Metric; MPN RC0603FR-074K7L; DigiKey 311-4.70KHRCT-ND
R20, R21, R22, R23, R24, R25, R27: 0R DNP; R_0603_1608Metric; MPN RC0603JR-070RL; DigiKey 311-0.0GRCT-ND; not fitted
TP16: 3V3; TestPoint_Pad_D1.5mm
TP17: GND; TestPoint_Pad_D1.5mm
U2: TPS70933QDBVRQ1; SOT-23-5; MPN TPS70933QDBVRQ1; DigiKey 296-40931-1-ND

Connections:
3V3_AMP: R26.2, R27.2; also elsewhere on the board
5V_RADAR: J5.1; also elsewhere on the board
+3V3: C12.1, F4.1, R26.1, TP16.1, U2.5 (OUT); also elsewhere on the board
+5V: R12.1; also elsewhere on the board
/3.3 V, Pi link, sensors, radar, echo-ref/3V3_SENS: F4.2, J6.1, J10.1, J11.1
/3.3 V, Pi link, sensors, radar, echo-ref/LDO_IN: C11.1, R12.2, U2.1 (IN)
/3.3 V, Pi link, sensors, radar, echo-ref/LD_TX: J5.3, R19.1
/3.3 V, Pi link, sensors, radar, echo-ref/PI_3V3: J3.1, R13.1, R27.1, U2.3 (EN)
/3.3 V, Pi link, sensors, radar, echo-ref/PI_BCLK: J3.7, R14.1
/3.3 V, Pi link, sensors, radar, echo-ref/PI_DIN: J4.2, R18.1, R23.1
/3.3 V, Pi link, sensors, radar, echo-ref/PI_DOUT: J4.4, R16.1
/3.3 V, Pi link, sensors, radar, echo-ref/PI_LRCLK: J4.1, R15.1
/3.3 V, Pi link, sensors, radar, echo-ref/PI_RXD: J3.6, R19.2
/3.3 V, Pi link, sensors, radar, echo-ref/PI_TXD: J3.4, J5.4
/3.3 V, Pi link, sensors, radar, echo-ref/RS_BCLK: J7.2, R20.2
/3.3 V, Pi link, sensors, radar, echo-ref/RS_LRCLK: J7.3, R21.2
/3.3 V, Pi link, sensors, radar, echo-ref/RS_OUT: J7.5, R23.2
/3.3 V, Pi link, sensors, radar, echo-ref/RS_REF: J7.4, R22.2
/3.3 V, Pi link, sensors, radar, echo-ref/RS_SCL: J7.8, R25.2
/3.3 V, Pi link, sensors, radar, echo-ref/RS_SDA: J7.7, R24.2
AMP_MUTE_N: J3.9, R17.1; also elsewhere on the board
GND: C11.2, C12.2, J3.5, J3.8, J4.3, J5.2, J6.2, J7.1, J7.6, J10.2, J11.2, R13.2, R17.2, R18.2, TP17.1, U2.2 (GND); also elsewhere on the board
I2C_SCL: J3.3, J6.4, J10.4, J11.4, R25.1; also elsewhere on the board
I2C_SDA: J3.2, J6.3, J10.3, J11.3, R24.1; also elsewhere on the board
I2S_BCLK: R14.2, R20.1; also elsewhere on the board
I2S_DOUT: R16.2, R22.1; also elsewhere on the board
I2S_LRCLK: R15.2, R21.1; also elsewhere on the board

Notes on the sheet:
3.3 V LDO (follows the Pi 3V3)
Pi signal leads (wire pads, 2.54 mm; 13 leads to three housings at the Pi, gpio-leads.md)
XH headers (JST XH 2.50 mm) - radar, touch board
Echo-reference (D4a) - default topology A: all links OPEN
V17: Raspberry Pi publishes no current rating for the Pi 5 header 3V3 pins -> 3.3 V LDO on this board (brief item 4). U2 TPS70933: 2.7-30 V in (survives the NID OVP 6.4-7.5 V), 150 mA, EN follows the Pi 3V3 (pin 1 lead, ~33 uA). Loads: TAS5756M DVDD/AVDD/CPVDD 35 mA (SLAS988B 7.12) + touch/BME680/V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
